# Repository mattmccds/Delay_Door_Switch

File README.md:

# Delay Door Switch

[![CC BY-NC-SA 4.0][cc-by-nc-sa-shield]][cc-by-nc-sa]

### Overview

The goal for this project was to make walking out of my garage, while the door closes, less of a race.  This is most likely an over-engineered solution to solve the problem but it does exactly what I wanted and is a fun use of a 555 timer.  The switch replaces the momentary switch used by my garage door opener but could be used anywhere a momentary switch is used to operate something.

The switch has two buttons: one closes the door immediately (zero delay) while the other delays 5 seconds before operating the door.  The delays are adjustable by selecting different component values, as detailed below.

The design includes both a printed circuit board and 3d printed enclosure.  No firmware is required.

## Delay Door Switch PCB

The PCB is available for order on [PCBWay Projects](https://www.pcbway.com/project/shareproject/Door_Delay_Switch_7a1f7a34.html).

| Front | Back |
|-------|------|
|  |  |

### Schematic

### Theory of Operation

For my garage door opener, pressing a normally-open momentary switch shorts two wires together causing the door to open or close.  The wires carry a 24VAC signal which was an important fact when selecting a solid state relay.  Other door openers or devices may differ in operation or signal levels so always check your own wiring.

To emulate a button press I selected a solid-state SPST-NO relay which was rated for AC signals (note that some solid-state relays only allow current in one direction so only work for DC signals).  When activated, the relay shorts the two wires just like the momentary button.  The zero delay button is wired in parallel with the relay so it operates independently from the delay circuit and does not require battery power.

Generating the delayed pulse to operate the relay was a little tricky.  One design requirement was an ultra-low standby power draw to maximize battery life.  Also keeping it simple and cheap meant anything with firmware was out.  I ended up using a two-timer architecture based around TI's [TPL5111 Nano-Power System Timer](https://www.ti.com/lit/ds/symlink/tpl5111.pdf) and a standard 555 timer.

The TPL5111 can run off a coin-cell battery, has an ultra-low (35nA typ) standby current and provides push-button operation so it fits the application perfectly.  A power switch controlled by the TPL5111 disconnects power from the remaining circuitry eliminating any quiescent current draw from those parts greatly reducing battery consumption.

The second timer is a standard 555 configured with a power-on delay.  After the delay time, the relay is activated by driving the SSR's LED.  The 555 remains in this state until it is powered off by the TPL5111.

The resulting interaction between the two timers generates a delayed pulse with the delay time set by the 555 power-on delay and the pulse length set by the TPL5111 activation period (TPL5111 active time - 555 power-on delay time = button press pulse length).  Luckily for the application we do not need either of these time periods to be very exact so standard resistor and capacitor tolerances are acceptable.  The component value calculations for these delay times are discussed in the next section.

The CR1220 battery choice was mostly arbitrary based on what I had on-hand.  There are other options that would work just as well or better.  Using rough calculations, one coin-cell should provide more than 1000+ button presses so works plenty fine for my application which may only close the door once per day.  The zero delay button uses no power and can operate even if the battery is drained.

### Delay Setting Calculations

Notes:

* The TPL5111 power-on time must be longer than the 555 delay time otherwise the relay pulse will not occur.
* The pulse time for the relay needs to be adjusted depending on the device being controlled.
* The longer the pulse is active the more power is used, reducing the clicks per battery life ratio.

#### To set the TPL5111 power-on time:

In one-shot mode, the TPL5111 will activate once per button click (built-in input debouncing is provided).

The delay time is set by adjusting the resistance value on pin 3 via the R2 and R3 resistors.  The two parallel resistors allow fine tuning of the resistance using standard E96 values but only one resistor is required if a standard value is close enough.

For my garage door, I selected a 9.09K resistor for R2 and left R3 unpopulated.  This sets the delay time slightly longer than 5.5 seconds based on using Equation 1 with coefficient Set 2 from [Page 12](https://www.ti.com/lit/ds/symlink/tpl5111.pdf#page=12) of the data sheet.

(-2651.8889-100*5.5)%7D%7D%7B2*-0.1284%7D%5Cbig)%20%3D%209055%20%20%5COmega%20)

For simplicity, [Page 13](https://www.ti.com/lit/ds/symlink/tpl5111.pdf#page=13) of the data sheet has a table of calculated resistor values.

#### To set the LM555 power-on delay time:

The 555 timer uses R1 and C1 to set the power-on delay time using the formula T = 1.1 * R1 * C1.  Selecting values of 453K and 10uF for R1 and C1 we get a delay slightly less than 5 seconds.

The relay pulse time is determined by how long the TPL5111 remains active after the 555 delay time.  For this example, the pulse time will be slightly longer than half a second (5.582s - 4.983s = 0.599s).

### 555 Power-On Delay Circuit

There are many configurations for the 555 timer.  The following circuit demonstrates a 555 timer that will set the output high after an initial power-on delay time.  The resistor and capacitor values are calculated using the formula T = 1.1 * R * C.

[Circuit Simulation](https://www.falstad.com/circuit/circuitjs.html?ctz=CQAgjCAMB0l3BWEBmAHAJmgdgGzoRmACzICcpkORICONNkNApgLRhgBQYOSyC64MAOQ5UggdUgcA8jSHhcNHIzCLGUgO4p0jVIyLcQeqBwDG23Y2Q7wRSVFjxI5F67fkoJgOYWUI33wC6hwATr7oWMI2yP76CMjwHFoGdMYI8sZSPnZiERJEuahiwVrWjDpiZSDoRCXVtUZWNplmICnVkW2GMXQqrMXeXXQ9Qyj8nprgyo31liZa7ALG3HPIHADO4jOL1ZADjABmAIYANutMHABKWxU3DeptjEgPMAhJbcuK6QKqve-ftmoBRUdnm4U6VRqdQBaXkxEk70Cu0qNlukyRUPC90RNnh4T2JgAJtUin46OhSXlquAAHIGArvCm5CGozqTJlkgKxDgAe3A2k8BkgAmejjgpFwtHwnl4nmQKF2nmiIB5AFcAC4ABw1HCAA)

### Bill of Materials

|   Ref   |   Value                    |   Digikey P/N   |  Alternate P/N |
|:-------:|:---------------------------|:---------------:|:---------------:|
| BT1     | CR1220 Battery Holder      | [2057-BH-44C-5-ND](https://www.digikey.com/en/products/detail/adam-tech/BH-44C-5/13537709) |
| C1,C5   | 10uF Capacitor 0805        | [1276-2935-1-ND](https://www.digikey.com/en/products/detail/samsung-electro-mechanics/CL21B106KQQNFNE/3888593) |
| C2,C3   | 0.1uF Capacitor 0603       | [1276-1935-1-ND](https://www.digikey.com/en/products/detail/samsung-electro-mechanics/CL10B104KB8NNWC/3887593) |
| C4      | 10nF Capacitor 0603        | [1276-1009-1-ND](https://www.digikey.com/en/products/detail/samsung-electro-mechanics/CL10B103KB8NNNC/3886667) |
| D1      | 1N4148 Diode SOD-123F      | [1N4148WRHGCT-ND](https://www.digikey.com/en/products/detail/taiwan-semiconductor-corporation/1N4148W-RHG/7357065) |
| J1      | 2.54mm Terminal Block      | [732-691210910002-ND](https://www.digikey.com/en/products/detail/würth-elektronik/691210910002/10668428) |
| R1      | 453K Resistor 0603         | [RMCF0603FT453KCT-ND](https://www.digikey.com/en/products/detail/stackpole-electronics-inc/RMCF0603FT453K/1761122) |
| R2      | 9.09K Resistor 0603        | [RMCF0603FT9K09CT-ND](https://www.digikey.com/en/products/detail/stackpole-electronics-inc/RMCF0603FT9K09/1760881) |
| R4      | 301 Resistor 0603          | [RMCF0603FT301RCT-ND](https://www.digikey.com/en/products/detail/stackpole-electronics-inc/RMCF0603FT301R/1760800) |
| R5      | 10K Resistor 0603          | [RMCF0603FT10K0CT-ND](https://www.digikey.com/en/products/detail/stackpole-electronics-inc/RMCF0603FT10K0/1761235) |
| SW1,SW2 | PTS810 Switch              | [CKN10878CT-ND](https://www.digikey.com/en/products/detail/c-k/PTS810-SJS-250-SMTR-LFS/4142163) |
| U1      | TPL5111 Nano-Power Timer   | [296-42621-1-ND](https://www.digikey.com/en/products/detail/texas-instruments/TPL5111DDCT/5358032) |
| U2      | LMC555CM Timer VSSOP-8     | [LMC555CMMX/NOPBCT-ND](https://www.digikey.com/en/products/detail/texas-instruments/LMC555CMMX-NOPB/367381) |
| U3      | TS5A3166DBVR Analog Switch | [296-17740-1-ND](https://www.digikey.com/en/products/detail/texas-instruments/TS5A3166DBVR/716904) | [MAX4626EUK+TCT-ND](https://www.digikey.com/en/products/detail/analog-devices-inc-maxim-integrated/MAX4626EUK-T/1016411) |
| U4      | C247S Solid-State Relay    | [306-1309-ND](https://www.digikey.com/en/products/detail/coto-technology/C247S/3961372) |
|  | 3D Printed Case | | |
| 2 | M2.5-0.45 x 16mm Screws | | [54FR55](https://www.grainger.com/product/GRAINGER-APPROVED-Machine-Screw-M2-5-0-45-Thread-54FR55) |

## Delay Door Switch Case

A 3d printed two-button case was designed in Fusion 360 to house the board.  The case's intended usage is indoors therefore not water tight and was printed in PLA on an FDM printer.

The case and buttons were printed on an Ender 3 Pro using a 0.2mm layer height.  No supports are required.  

A two-stage process was used for the integrated button numbers.  See this [video](https://youtu.be/0Sla-vIsvh4) for details on the process.  Basically, print the numbers first, change the filament color, print the rest of the button.  When slicing, the numbers and buttons have to be aligned exactly on the build plate and z-hop needs to be enabled to prevent the nozzle dragging through the numbers.

The case and buttons can be modified from the included STEP model if needed, or you can just print the other files if you like it as is.

#### Files:

| Description | File |
|:-----------|:-----:|
| Full Model (STEP Format)     | [`Delay_Door_Switch_Case.step`](case/Delay_Door_Switch_Case.step)
| Door Switch Front Case       | [`Door_Switch_Case.3mf`](case/Door_Switch_Case.3mf) |
| Door Switch Back Lid         | [`Door_Switch_Lid.3mf`](case/Door_Switch_Lid.3mf)  |
| Button Numbers (print first) | [`Button_Numbers.stl`](case/Button_Numbers.stl) |
| Buttons (print second)       | [`Buttons.stl`](case/Buttons.stl) |

## Assembly

The switch PCB is sandwiched between the front case and the back lid and held in place with two M2.5-0.45 x 16mm flat-head machine screws.

#### Assembly Steps

1. Drop the buttons into the front case (making sure the numbers are right-side up).
2. Feed the wire through the hole in the case.
3. Attach the wire to the PCB terminal block.
4. Place the PCB with the front-side facing the buttons.
5. Place the back lid on making sure to check that the PCB is aligned with the mounting holes.
6. Insert the two M2.5x16mm screws to hold the switch together.
7. Verify the buttons click properly.
8. Attach the switch to the wall with drywall (or similar) screws.

## License

[![CC BY-NC-SA 4.0][cc-by-nc-sa-image]][cc-by-nc-sa]

[cc-by-nc-sa]: http://creativecommons.org/licenses/by-nc-sa/4.0/
[cc-by-nc-sa-image]: https://licensebuttons.net/l/by-nc-sa/4.0/88x31.png
[cc-by-nc-sa-shield]: https://img.shields.io/badge/License-CC%20BY--NC--SA%204.0-lightgrey.svg

This work is licensed under the *non-commercial* [Creative Commons Attribution-NonCommercial-ShareAlike 4.0 International License][cc-by-nc-sa] due to the use a personal/hobbyist edition of [Autodesk Fusion 360](https://www.autodesk.com/products/fusion-360) for parts of the design.

No warranties or guarantees of any kind.

## References & Other Reading

* [Generating a delayed pulse with one 555 timer upon powering up the circuit](https://electronics.stackexchange.com/questions/245753/generating-a-delayed-pulse-with-one-555-timer-upon-powering-up-the-circuit)
    * [Follow up post with value calculations](https://electronics.stackexchange.com/questions/415378/generating-a-delayed-pulse-of-0-5sec-with-one-555-timer-upon-powering-up-the-cir)
* [Creating two delayed pulses from a 556](https://forum.allaboutcircuits.com/threads/creating-2-delayed-pulses-from-a-556.129043/)
* [Lots of 555 timer circuits](http://www.555-timer-circuits.com)
* [Pulse Delay Circuit Using 555 Timer](https://forum.allaboutcircuits.com/threads/pulse-delay-circuit-using-555-timer.149724/)
* Part Datasheets
	* [TPL5110 Nano-Power System Timer](https://www.ti.com/lit/ds/symlink/tpl5110.pdf)
	* [TPL5111 Nano-Power System Timer](https://www.ti.com/lit/ds/symlink/tpl5111.pdf)
	* [LMC555 CMOS Timer](https://www.ti.com/lit/ds/symlink/lmc555.pdf)

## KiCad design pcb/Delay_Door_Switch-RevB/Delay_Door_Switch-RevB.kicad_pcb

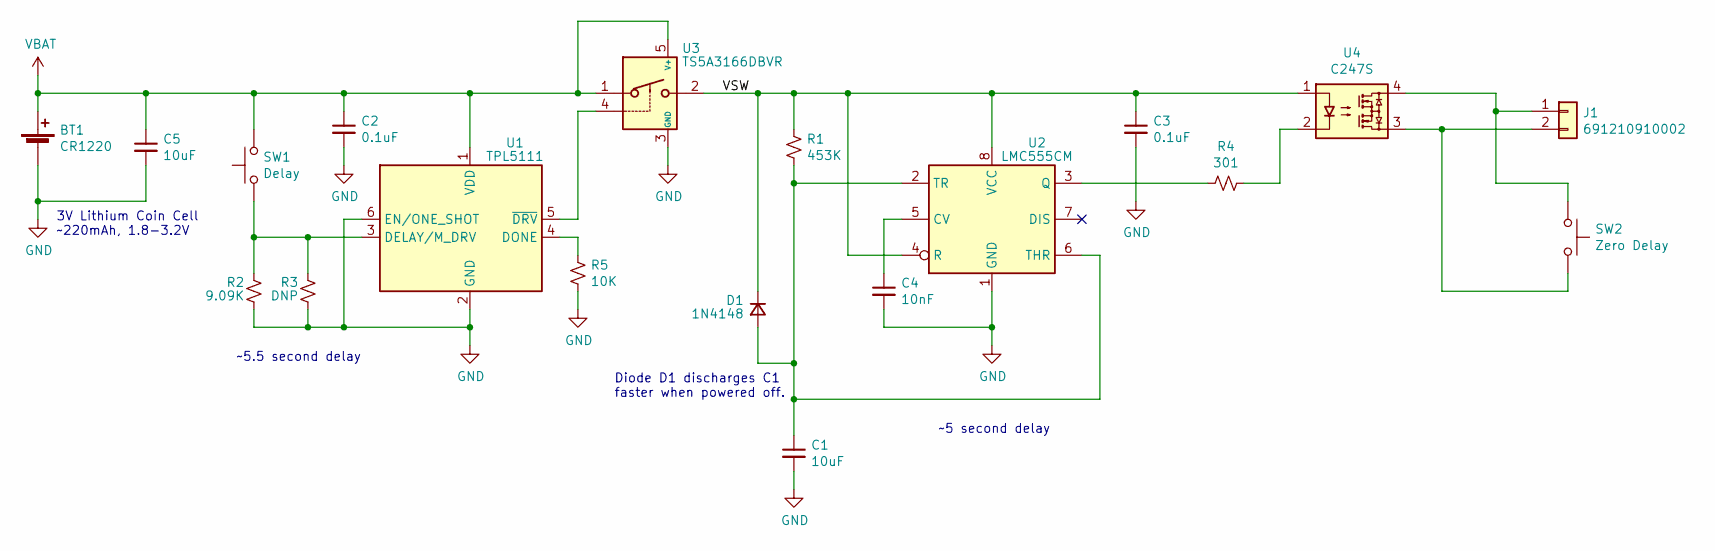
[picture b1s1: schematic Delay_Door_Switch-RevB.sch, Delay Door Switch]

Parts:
BT1: CR1220; BH-44G-5
C1, C5: 10uF; C_0805_2012Metric
C2, C3: 0.1uF; C_0603_1608Metric
C4: 10nF; C_0603_1608Metric
D1: 1N4148; D_SOD-123F
J1: 691210910002; Wuerth_WR-TBL_691210910002_1x02_P2.54mm_Horizontal
R1: 453K; R_0603_1608Metric
R2: 9.09K; R_0603_1608Metric
R3: DNP; R_0603_1608Metric
R4: 301; R_0603_1608Metric
R5: 10K; R_0603_1608Metric
SW1: Delay; SW_SPST_PTS810
SW2: Zero Delay; SW_SPST_PTS810
U1: TPL5111; SOT-23-6
U2: LMC555CM; VSSOP-8_3.0x3.0mm_P0.65mm
U3: TS5A3166DBVR; SOT-23-5
U4: C247S; SOP-4_4.4x4.3mm_P2.54mm

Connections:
/VSW: C3.1, D1.1 (K), R1.1, U2.4 (R), U2.8 (VCC), U3.2, U4.1
GND: BT1.2 (-), C1.2, C2.2, C3.2, C4.2, C5.2, R2.2, R3.2, R5.2, U1.2 (GND), U1.6 (EN/ONE_SHOT), U2.1 (GND), U3.3 (GND)
unnamed: C1.1, D1.2 (A), R1.2, U2.2 (TR), U2.6 (THR)
unnamed: C4.1, U2.5 (CV)
unnamed: J1.1, SW2.2, U4.4
unnamed: J1.2, SW2.1, U4.3
unnamed: R2.1, R3.1, SW1.1, U1.3 (DELAY/M_DRV)
unnamed: R4.1, U4.2
unnamed: R4.2, U2.3 (Q)
unnamed: R5.1, U1.4 (DONE)
unnamed: U1.5 (~DRV), U3.4
VBAT: BT1.1 (+), C2.1, C5.1, SW1.2, U1.1 (VDD), U3.1, U3.5 (V+)

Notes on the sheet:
~~5.5 second delay
~~5 second delay
3V Lithium Coin Cell ~~220mAh, 1.8-3.2V
Diode D1 discharges C1 faster when powered off.

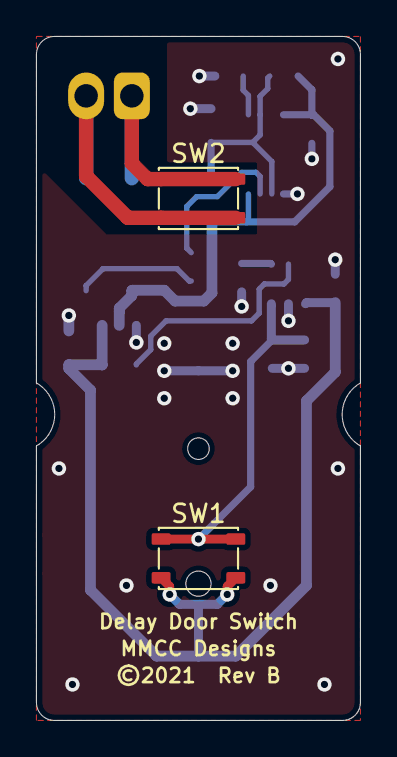
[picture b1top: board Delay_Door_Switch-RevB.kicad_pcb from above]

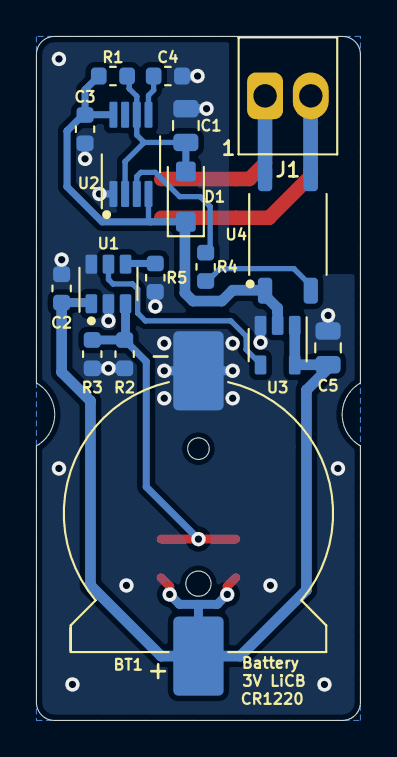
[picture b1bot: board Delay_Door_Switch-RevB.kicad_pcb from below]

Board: 2 copper layers, 18.0 x 38.0 mm, 19 parts (17 on the bottom side), 12 nets.

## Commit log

2022-05-12 Fixed typo. Added link to PCBWay Project.

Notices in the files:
pcb/Delay_Door_Switch-RevB/Delay_Door_Switch-RevB.kicad_pcb:
MMCC Designs ©2021
©2021  Rev B
pcb/Delay_Door_Switch-RevB/Delay_Door_Switch-RevB.sch:
©2021
